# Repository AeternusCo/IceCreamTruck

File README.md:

# Ice Cream Truck

A drop-in replacement PCB for Minivan cases with choc v1 switches.

**N.B.** At the date of publication, some keys don't exist so they'll either need to use smaller key sizes or 3d printed keys.

PCB has been tested, but order at your own risk.

## Features

- STM32F072 (or F042) MCU
- Drop-in compatibility with existing minivan cases
- Choc v1 switch footprints

## Firmware

ICT runs QMK. Firmware has not been merged into upstream, but should be available in the AeternusCo fork [here](https://github.com/AeternusCo/qmk_firmware).

## Ordering

Generate gerbers, upload to fab house of your choice, pay.

## Images

## License

All files are licensed under CERN-OHL-P v2.

See [LICENSE](/LICENSE) file for more details.

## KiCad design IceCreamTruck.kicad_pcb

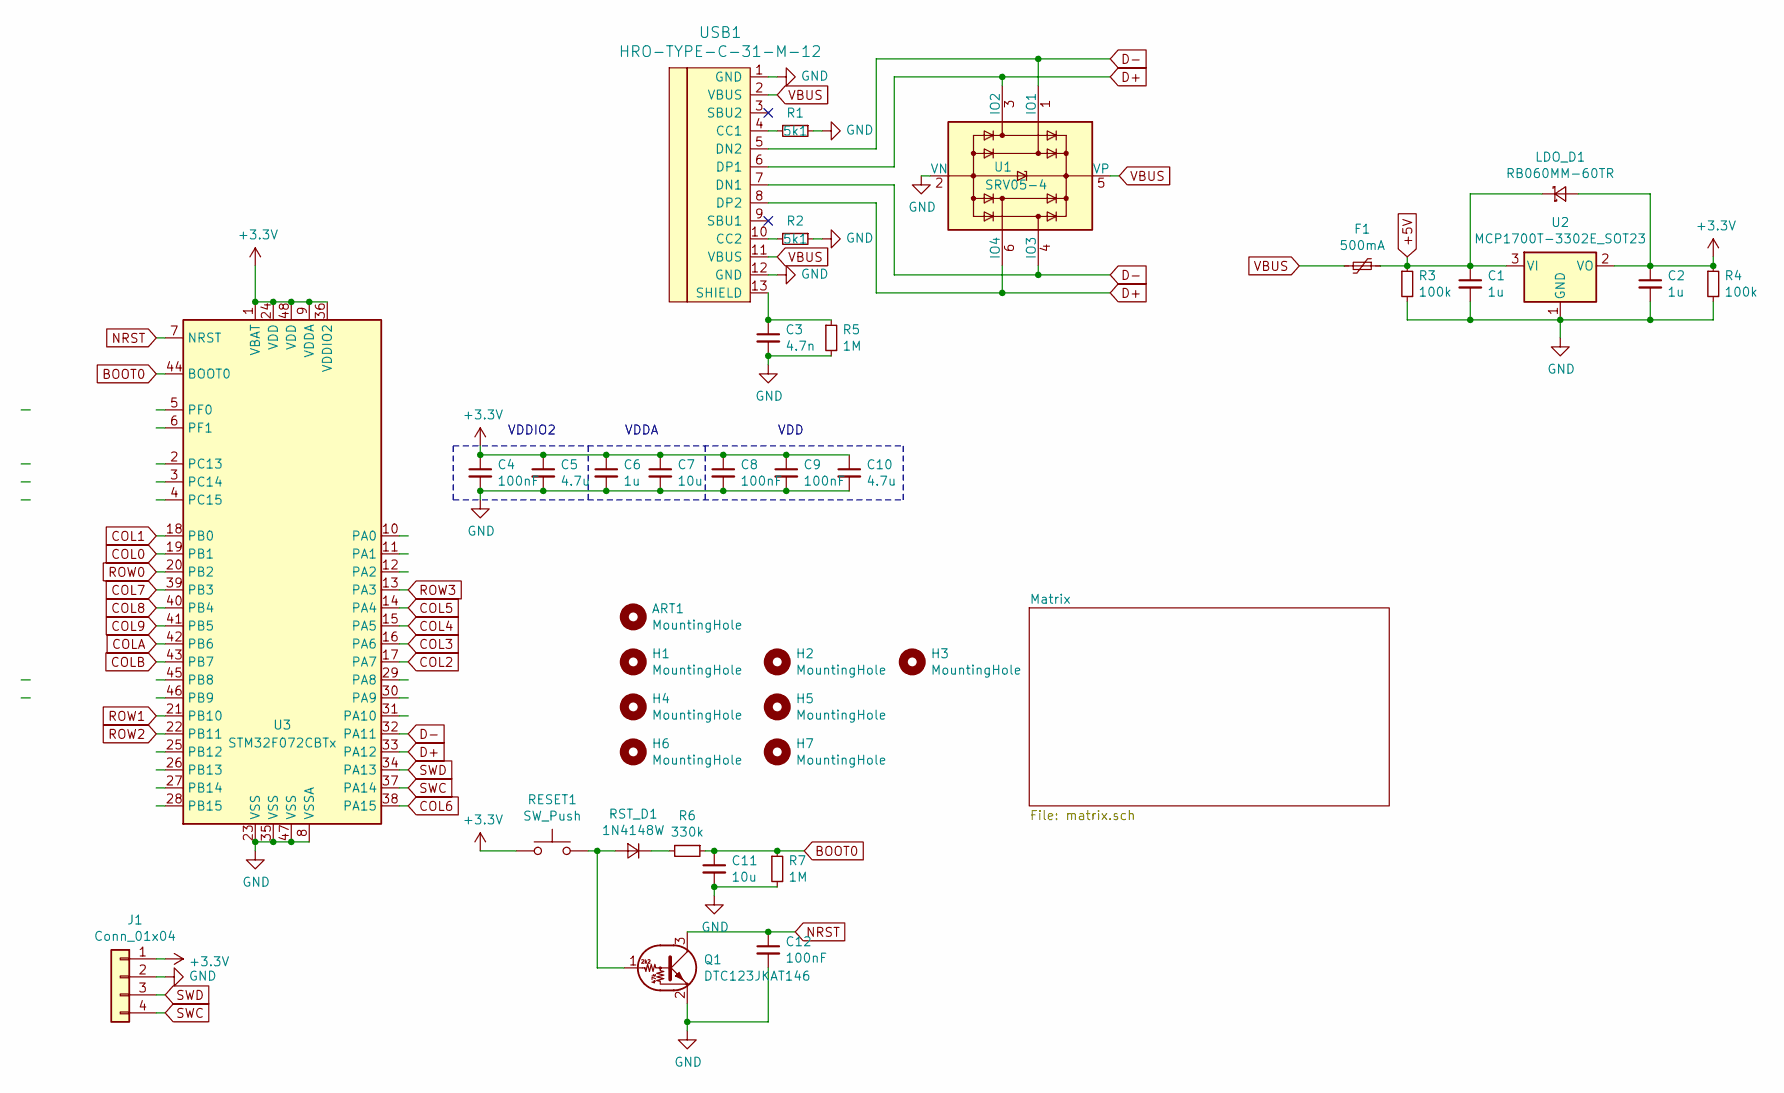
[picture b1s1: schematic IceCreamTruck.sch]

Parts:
ART1: MountingHole; AeternusDecorumLogo18x18
C1, C2, C6: 1u; C_0402_1005Metric
C3: 4.7n; C_0402_1005Metric
C4, C8, C9, C12: 100nF; C_0402_1005Metric
C5, C10: 4.7u; C_0402_1005Metric
C7, C11: 10u; C_0402_1005Metric
F1: 500mA; Fuse_1206_3216Metric
H1, H2, H3, H4, H5, H6, H7: MountingHole; MountingHole_2.2mm_M2_Pad
J1: Conn_01x04; PinHeader_1x04_P2.54mm_Vertical
LDO_D1: RB060MM-60TR; D_SOD-123F
Q1: DTC123JKAT146; SOT-23
R1, R2: 5k1; R_0402_1005Metric
R3, R4: 100k; R_0402_1005Metric
R5, R7: 1M; R_0402_1005Metric
R6: 330k; R_0402_1005Metric
RESET1: SW_Push; PinHeader_1x02_P2.54mm_Vertical
RST_D1: 1N4148W; D_0603_1608Metric
U1: SRV05-4; SOT-23-6
U2: MCP1700T-3302E_SOT23; SOT-23
U3: STM32F072CBTx; LQFP-48_7x7mm_P0.5mm
USB1: HRO-TYPE-C-31-M-12

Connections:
+3V3: C2.1, C4.1, C5.1, C6.1, C7.1, C8.1, C9.1, C10.1, J1.1, LDO_D1.2 (A), R4.1, RESET1.1, U2.2 (VO), U3.1 (VBAT), U3.9 (VDDA), U3.24 (VDD), U3.36 (VDDIO2), U3.48 (VDD)
+5V: C1.1, F1.1, LDO_D1.1 (K), R3.1, U2.3 (VI)
BOOT0: C11.1, R6.1, R7.1, U3.44 (BOOT0)
COL0: U3.19 (PB1); also elsewhere on the board
COL1: U3.18 (PB0); also elsewhere on the board
COL2: U3.17 (PA7); also elsewhere on the board
COL3: U3.16 (PA6); also elsewhere on the board
COL4: U3.15 (PA5); also elsewhere on the board
COL5: U3.14 (PA4); also elsewhere on the board
COL6: U3.38 (PA15); also elsewhere on the board
COL7: U3.39 (PB3); also elsewhere on the board
COL8: U3.40 (PB4); also elsewhere on the board
COL9: U3.41 (PB5); also elsewhere on the board
COLA: U3.42 (PB6); also elsewhere on the board
COLB: U3.43 (PB7); also elsewhere on the board
D+: U1.3 (IO2), U1.6 (IO4), U3.33 (PA12), USB1.6 (DP1), USB1.8 (DP2)
D-: U1.1 (IO1), U1.4 (IO3), U3.32 (PA11), USB1.5 (DN2), USB1.7 (DN1)
GND: C1.2, C2.2, C3.2, C4.2, C5.2, C6.2, C7.2, C8.2, C9.2, C10.2, C11.2, C12.2, J1.2, Q1.2 (E), R1.1, R2.1, R3.2, R4.2, R5.2, R7.2, U1.2 (VN), U2.1 (GND), U3.8 (VSSA), U3.23 (VSS), U3.35 (VSS), U3.47 (VSS), USB1.1 (GND), USB1.12 (GND)
NRST: C12.1, Q1.3 (C), U3.7 (NRST)
unnamed: C3.1, R5.1, USB1.13 (SHIELD)
unnamed: Q1.1 (B), RESET1.2, RST_D1.2 (A)
unnamed: R1.2, USB1.4 (CC1)
unnamed: R2.2, USB1.10 (CC2)
unnamed: R6.2, RST_D1.1 (K)
ROW0: U3.20 (PB2); also elsewhere on the board
ROW1: U3.21 (PB10); also elsewhere on the board
ROW2: U3.22 (PB11); also elsewhere on the board
ROW3: U3.13 (PA3); also elsewhere on the board
SWC: J1.4, U3.37 (PA14)
SWD: J1.3, U3.34 (PA13)
VBUS: F1.2, U1.5 (VP), USB1.2 (VBUS), USB1.11 (VBUS)

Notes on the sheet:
VDDIO2
VDDA
VDD

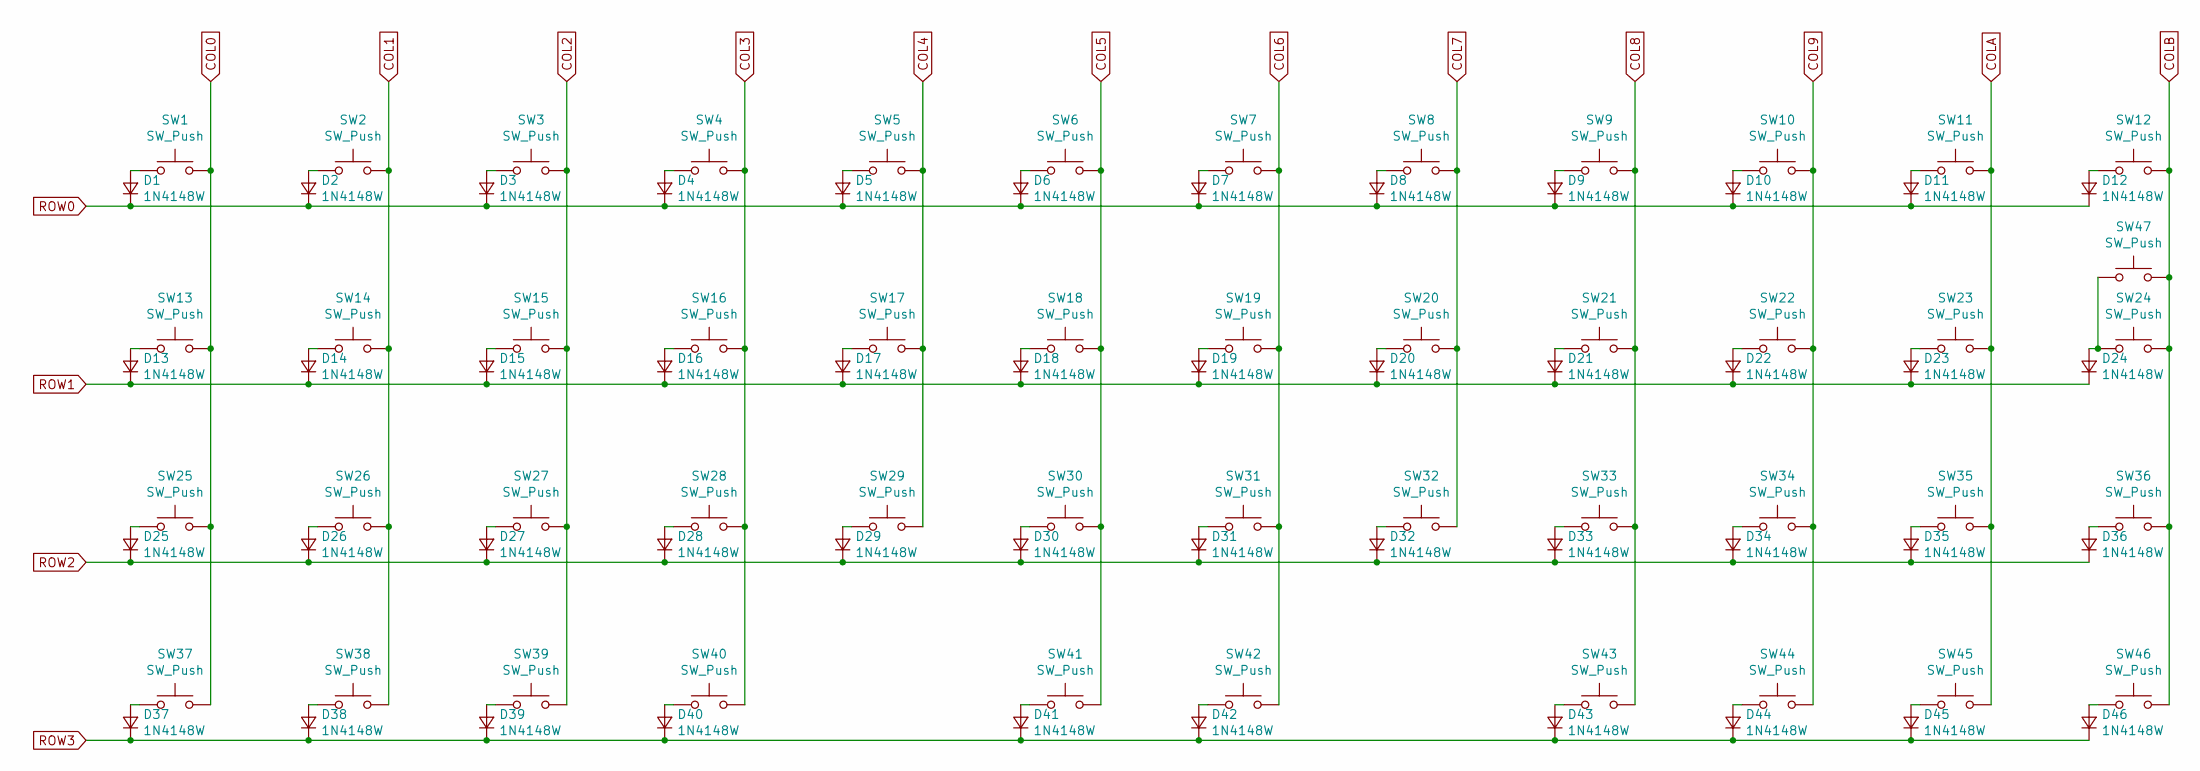
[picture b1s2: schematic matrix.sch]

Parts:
D1, D2, D3, D4, D5, D6, D7, D8, D9, D10, D11, D12, D13, D14, D15, D16, D17, D18, D19, D20, D21, D22, D23, D24, D25, D26, D27, D28, D29, D30, D31, D32, D33, D34, D35, D36, D37, D38, D39, D40, D41, D42, D43, D44, D45, D46: 1N4148W; D_0603_1608Metric
SW1, SW2, SW3, SW4, SW5, SW6, SW7, SW8, SW9, SW10, SW11, SW14, SW15, SW16, SW17, SW18, SW19, SW20, SW21, SW22, SW23, SW26, SW27, SW28, SW29, SW30, SW31, SW32, SW33, SW34, SW35, SW36, SW37, SW38, SW39, SW40, SW41, SW42, SW44, SW45, SW46, SW47: SW_Push; KailhChoc-1U
SW12, SW25: SW_Push; KailhChoc-1.75U
SW13: SW_Push; KailhChoc-1.25U
SW24, SW43: SW_Push; KailhChoc-1.5U

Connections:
COL0: SW1.2, SW13.2, SW25.2, SW37.2; also elsewhere on the board
COL1: SW2.2, SW14.2, SW26.2, SW38.2; also elsewhere on the board
COL2: SW3.2, SW15.2, SW27.2, SW39.2; also elsewhere on the board
COL3: SW4.2, SW16.2, SW28.2, SW40.2; also elsewhere on the board
COL4: SW5.2, SW17.2, SW29.2; also elsewhere on the board
COL5: SW6.2, SW18.2, SW30.2, SW41.2; also elsewhere on the board
COL6: SW7.2, SW19.2, SW31.2, SW42.2; also elsewhere on the board
COL7: SW8.2, SW20.2, SW32.2; also elsewhere on the board
COL8: SW9.2, SW21.2, SW33.2, SW43.2; also elsewhere on the board
COL9: SW10.2, SW22.2, SW34.2, SW44.2; also elsewhere on the board
COLA: SW11.2, SW23.2, SW35.2, SW45.2; also elsewhere on the board
COLB: SW12.2, SW24.2, SW36.2, SW46.2, SW47.2; also elsewhere on the board
unnamed: D1.2 (A), SW1.1
unnamed: D2.2 (A), SW2.1
unnamed: D3.2 (A), SW3.1
unnamed: D4.2 (A), SW4.1
unnamed: D5.2 (A), SW5.1
unnamed: D6.2 (A), SW6.1
unnamed: D7.2 (A), SW7.1
unnamed: D8.2 (A), SW8.1
unnamed: D9.2 (A), SW9.1
unnamed: D10.2 (A), SW10.1
unnamed: D11.2 (A), SW11.1
unnamed: D12.2 (A), SW12.1
unnamed: D13.2 (A), SW13.1
unnamed: D14.2 (A), SW14.1
unnamed: D15.2 (A), SW15.1
unnamed: D16.2 (A), SW16.1
unnamed: D17.2 (A), SW17.1
unnamed: D18.2 (A), SW18.1
unnamed: D19.2 (A), SW19.1
unnamed: D20.2 (A), SW20.1
unnamed: D21.2 (A), SW21.1
unnamed: D22.2 (A), SW22.1
unnamed: D23.2 (A), SW23.1
unnamed: D24.2 (A), SW24.1, SW47.1
unnamed: D25.2 (A), SW25.1
unnamed: D26.2 (A), SW26.1
unnamed: D27.2 (A), SW27.1
unnamed: D28.2 (A), SW28.1
unnamed: D29.2 (A), SW29.1
unnamed: D30.2 (A), SW30.1
unnamed: D31.2 (A), SW31.1
unnamed: D32.2 (A), SW32.1
unnamed: D33.2 (A), SW33.1
unnamed: D34.2 (A), SW34.1
unnamed: D35.2 (A), SW35.1
unnamed: D36.2 (A), SW36.1
unnamed: D37.2 (A), SW37.1
unnamed: D38.2 (A), SW38.1
unnamed: D39.2 (A), SW39.1
unnamed: D40.2 (A), SW40.1
unnamed: D41.2 (A), SW41.1
unnamed: D42.2 (A), SW42.1
unnamed: D43.2 (A), SW43.1
unnamed: D44.2 (A), SW44.1
unnamed: D45.2 (A), SW45.1
unnamed: D46.2 (A), SW46.1
ROW0: D1.1 (K), D2.1 (K), D3.1 (K), D4.1 (K), D5.1 (K), D6.1 (K), D7.1 (K), D8.1 (K), D9.1 (K), D10.1 (K), D11.1 (K), D12.1 (K); also elsewhere on the board
ROW1: D13.1 (K), D14.1 (K), D15.1 (K), D16.1 (K), D17.1 (K), D18.1 (K), D19.1 (K), D20.1 (K), D21.1 (K), D22.1 (K), D23.1 (K), D24.1 (K); also elsewhere on the board
ROW2: D25.1 (K), D26.1 (K), D27.1 (K), D28.1 (K), D29.1 (K), D30.1 (K), D31.1 (K), D32.1 (K), D33.1 (K), D34.1 (K), D35.1 (K), D36.1 (K); also elsewhere on the board
ROW3: D37.1 (K), D38.1 (K), D39.1 (K), D40.1 (K), D41.1 (K), D42.1 (K), D43.1 (K), D44.1 (K), D45.1 (K), D46.1 (K); also elsewhere on the board

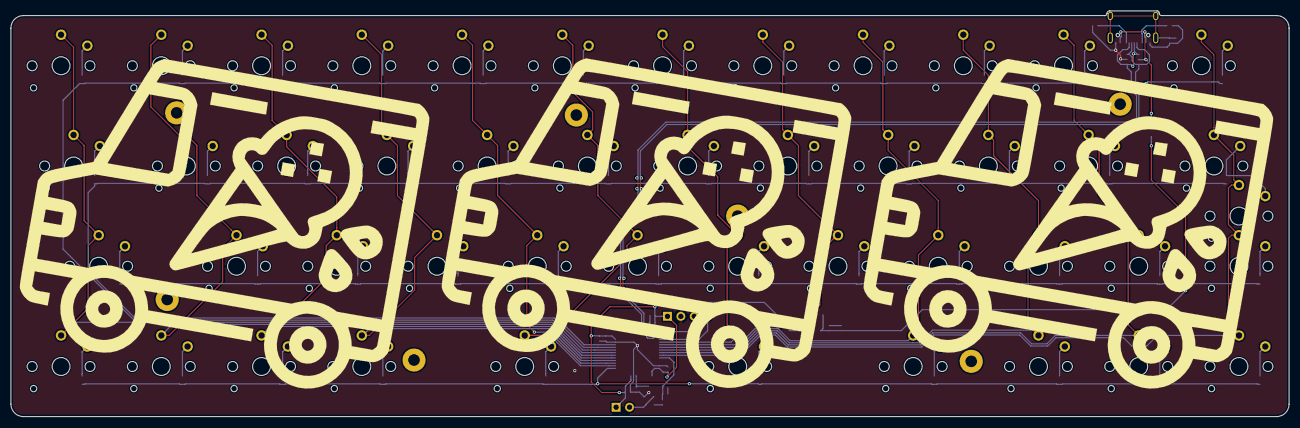
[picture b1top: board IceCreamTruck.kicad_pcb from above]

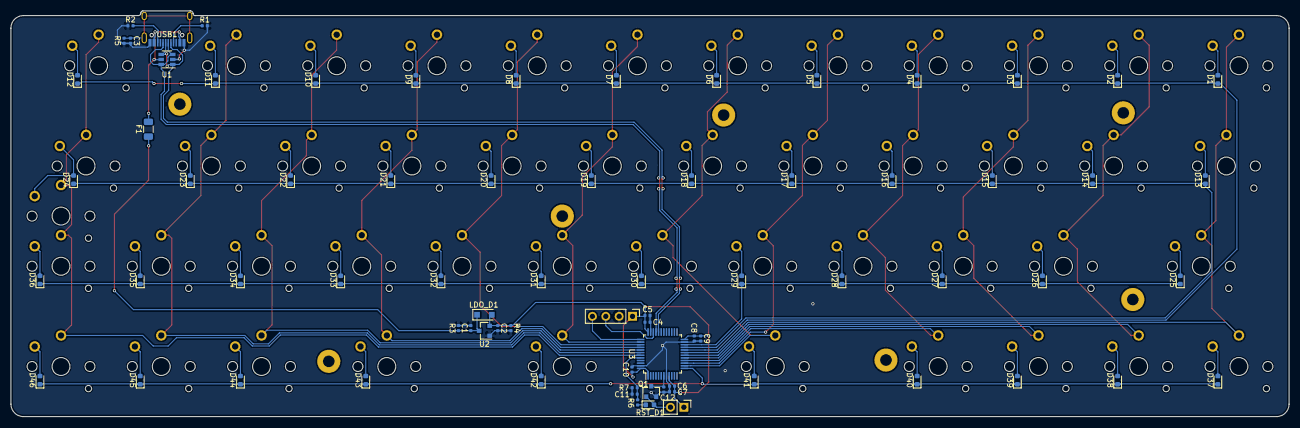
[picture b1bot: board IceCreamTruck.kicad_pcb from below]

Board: 2 copper layers, 242.9 x 77.1 mm, 130 parts (75 on the bottom side), 77 nets.

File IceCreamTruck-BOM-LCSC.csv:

Id,Comment,Designator,Footprint,Quantity,LCSC Part Number,,
5,1N4148W,"D38,D39,D37,D45,D46,D44,D16,D15,D13,D14,D8,D6,D7,D3,D4,D5,D2,D17,D18,D19,D20,D25,D26,D27,D28,D29,D30,D31,D32,RST_D1,D10,D12,D11,D9,D1,D22,D21,D23,D24,D33,D34,D35,D36,D40,D41,D43,D42",0603,47,C109002,,
8,STM32F072CBTx,U3,LQFP-48_7.0x7.0x0.5P,1,C88447,,
9,SRV05-4,U1,SOT-23-6,1,C85364,,
10,MCP1700T-3302E_SOT23,U2,SOT-23-3,1,C39051,,
11,10u,"C7,C11",0402,2,C15525,,
12,1u,"C1,C2,C6",0402,3,C52923,,
13,4.7n,C3,0402,1,C1538,,
14,100nF,"C8,C4,C9,C12",0402,4,C1525,,
15,4.7u,"C5,C10",0402,2,C23733,,
16,5k1,"R2,R1",0402,2,C25905,,
17,DTC123JKAT146,Q1,SOT-23-3,1,C111724,,
22,100k,"R3,R4",0402,2,C25741,,
23,330k,R6,0402,1,C25779,,
24,1M,"R5,R7",0402,2,C26083,,

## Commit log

2021-11-15 Initial commit.
2021-11-15 Added README and LICENSE.
